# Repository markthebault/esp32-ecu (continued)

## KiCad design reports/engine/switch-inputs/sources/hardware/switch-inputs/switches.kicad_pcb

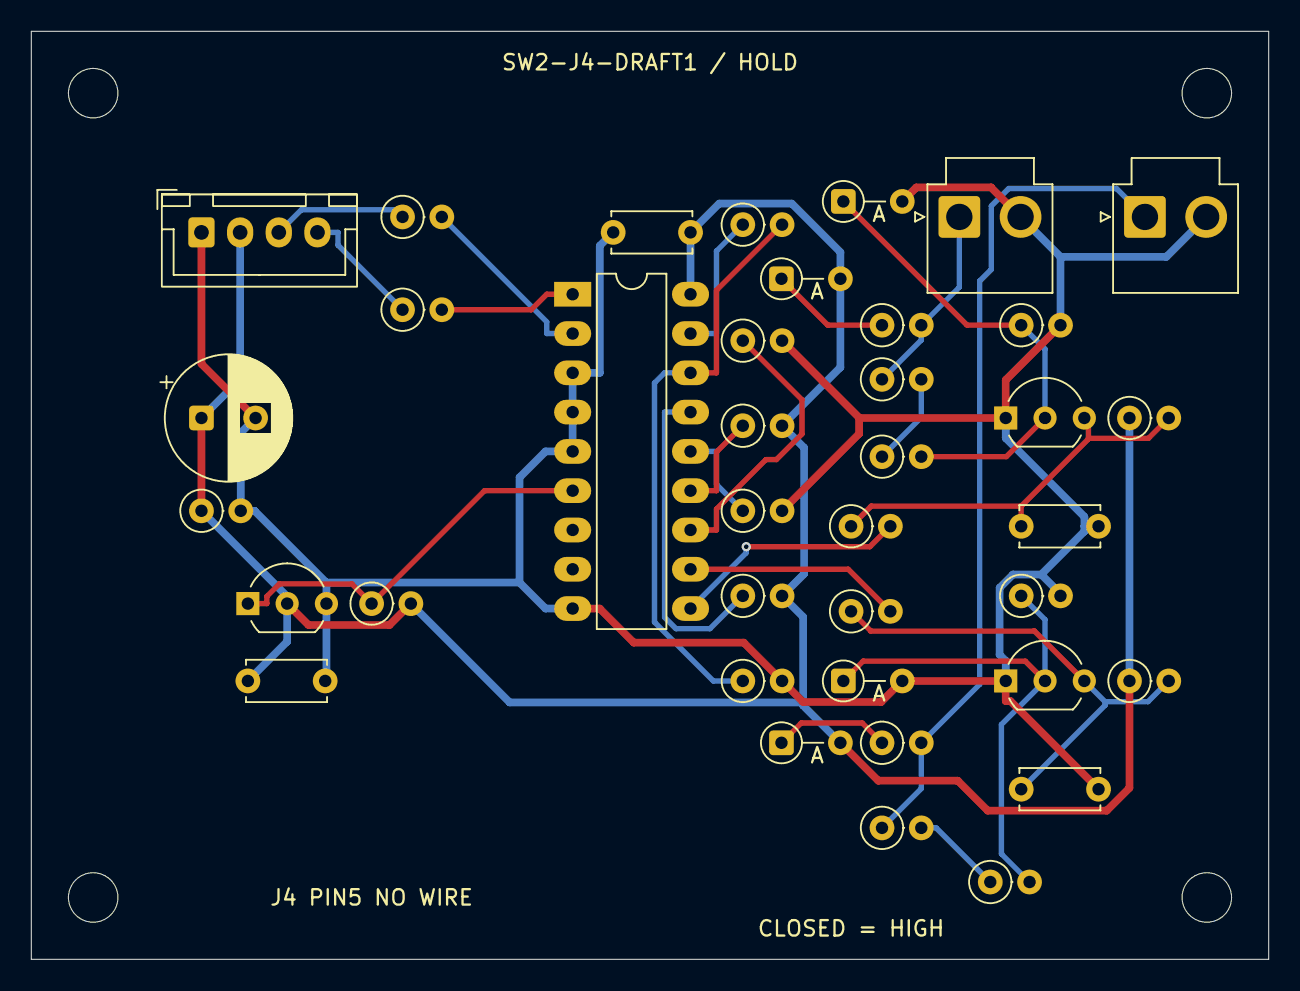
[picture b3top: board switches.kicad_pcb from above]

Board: 2 copper layers, 80.0 x 60.0 mm, 42 parts (0 on the bottom side), 25 nets.

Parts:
C1, C2: 100nF 50V; C_Disc_D5.0mm_W2.5mm_P5.00mm
C3, C4: 10nF 50V; C_Disc_D5.0mm_W2.5mm_P5.00mm
C5: 10uF 16V; CP_Radial_D8.0mm_P3.50mm
D1, D2, D3, D4: 1N4148-TAP; D_DO-35_SOD27_P3.81mm_Vertical_AnodeUp
H1, H2, H3, H4: M3 INSULATED MOUNT; MountingHole_3.2mm_M3
J1: INTERNAL J4 LINK; JST_XH_B4B-XH-A_1x04_P2.50mm_Vertical
J2: DRY CONTACT 0; JST_VH_B2P-VH_1x02_P3.96mm_Vertical
J3: DRY CONTACT 1; JST_VH_B2P-VH_1x02_P3.96mm_Vertical
Q1, Q2: 2N3904BU; TO-92_Inline_Wide
R1, R2: 2200R 1% 0.6W; R_Axial_DIN0207_L6.3mm_D2.5mm_P2.54mm_Vertical
R3, R4, R5, R6: 4990R 1% 0.6W; R_Axial_DIN0207_L6.3mm_D2.5mm_P2.54mm_Vertical
R7, R8, R18, R19: 100000R 1% 0.6W; R_Axial_DIN0207_L6.3mm_D2.5mm_P2.54mm_Vertical
R9, R10: 4700R 1% 0.6W; R_Axial_DIN0207_L6.3mm_D2.5mm_P2.54mm_Vertical
R11, R12, R17, R20: 1000R 1% 0.6W; R_Axial_DIN0207_L6.3mm_D2.5mm_P2.54mm_Vertical
R13, R14, R15, R16: 10000R 1% 0.6W; R_Axial_DIN0207_L6.3mm_D2.5mm_P2.54mm_Vertical
R21, R22: 100R 1% 0.6W; R_Axial_DIN0207_L6.3mm_D2.5mm_P2.54mm_Vertical
U1: MCP23008-E/P; DIP-18_W7.62mm_LongPads
U2: MCP121-300E/TO; TO-92_Inline_Wide

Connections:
+3V3: C1.1, C2.1, C5.1, D1.2, D2.2, J1.2, R9.1, R10.1, R14.2, R16.2, R19.2, R20.1, U1.18, U2.2
BASE0: D3.1, Q1.2, R4.2, R7.1
BASE1: D4.1, Q2.2, R6.2, R8.1
BIAS0: D1.1, R1.1
BIAS1: D2.1, R2.1
COL0: C3.1, Q1.3, R9.2, R11.1
COL1: C4.1, Q2.3, R10.2, R12.1
GND: C1.2, C2.2, C3.2, C4.2, C5.2, D3.2, D4.2, J1.1, J2.2, J3.2, Q1.1, Q2.1, R7.2, R8.2, R13.2, R15.2, R18.2, R20.2, U1.3, U1.4, U1.5, U1.9, U2.3
GP0: R11.2, U1.10
GP1: R12.2, U1.11
GP2: R13.1, U1.12
GP3: R14.1, U1.13
GP4: R15.1, U1.14
GP5: R16.1, U1.15
GP6: R17.2, R18.1, U1.16
GP7: R17.1, U1.17
MID0: R3.2, R4.1
MID1: R5.2, R6.1
RESET_N: R19.1, U1.6, U2.1
SCL: R22.2, U1.1
SCL_CARRIER: J1.4, R22.1
SDA: R21.2, U1.2
SDA_CARRIER: J1.3, R21.1
SW0: J2.1, R1.2, R3.1
SW1: J3.1, R2.2, R5.1
